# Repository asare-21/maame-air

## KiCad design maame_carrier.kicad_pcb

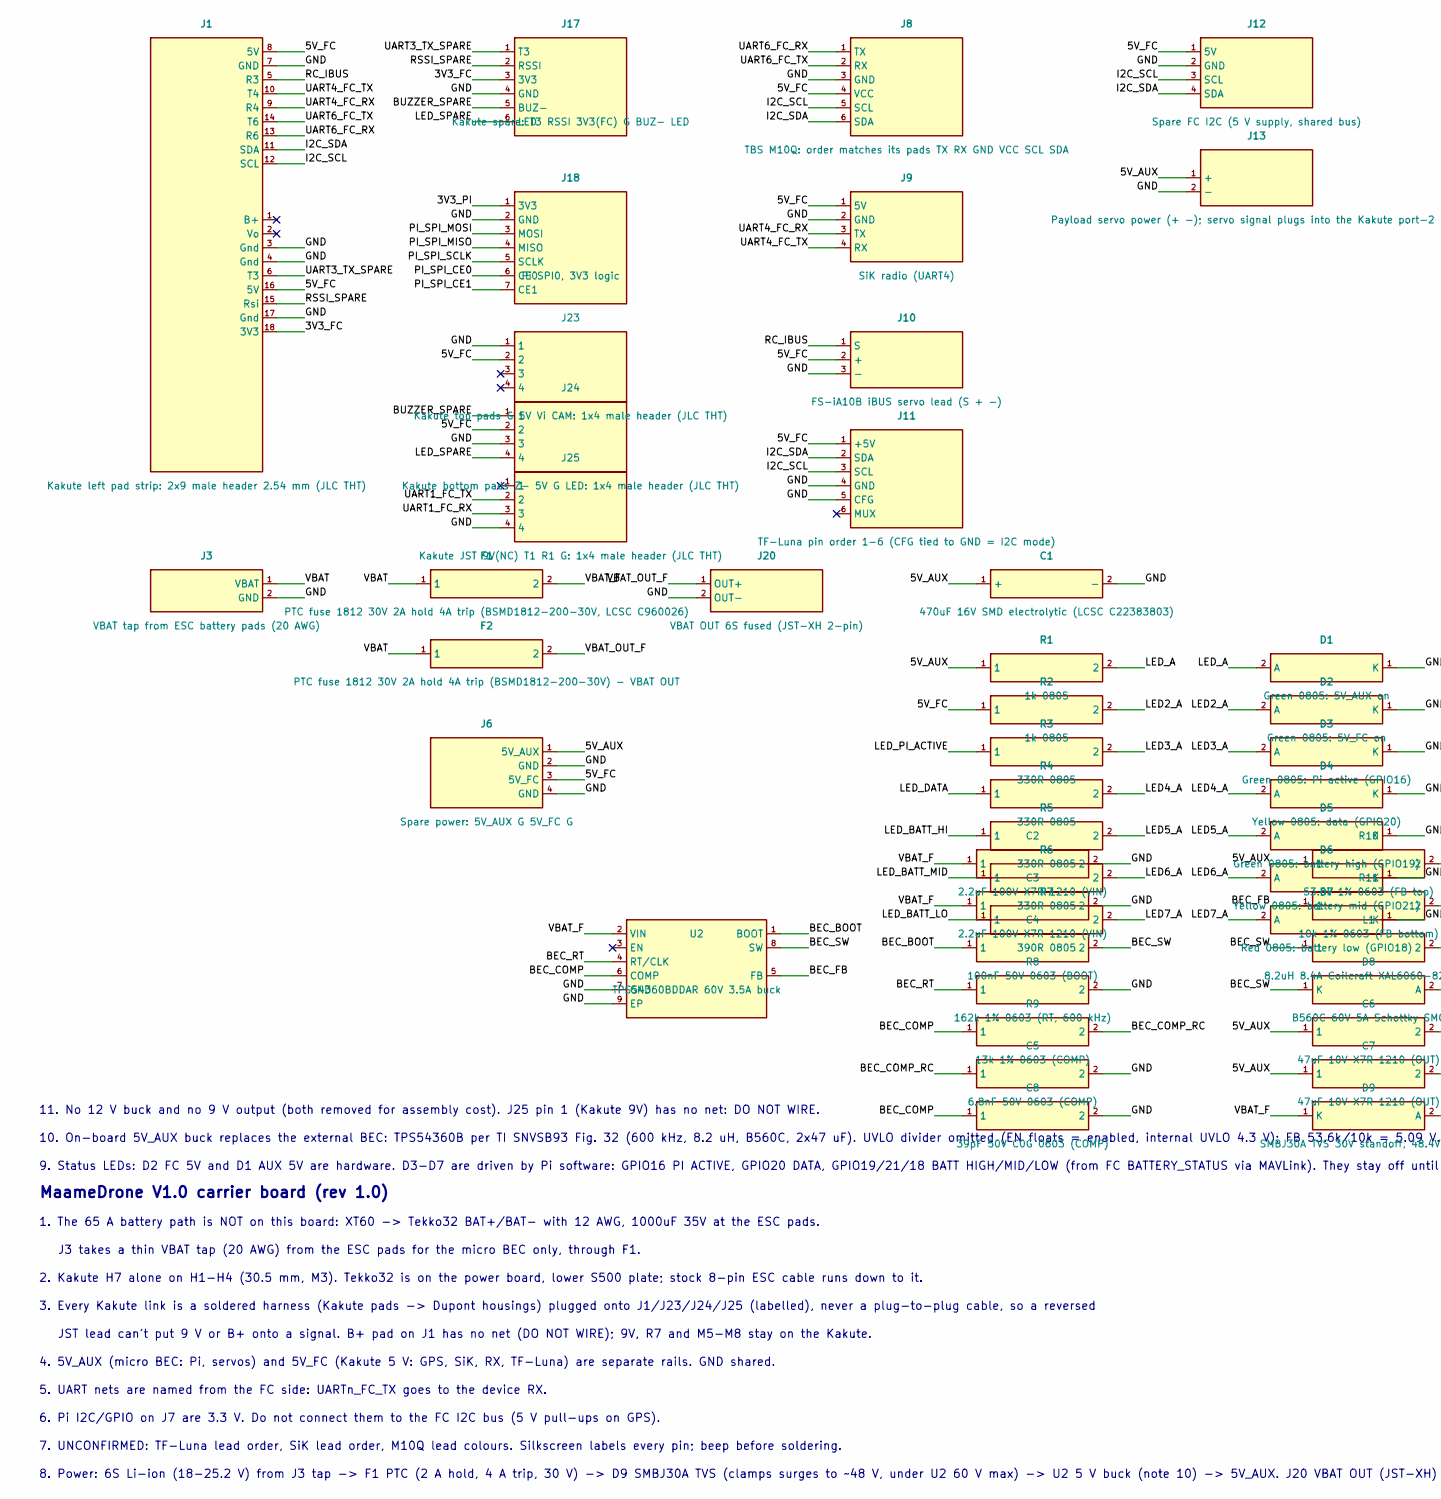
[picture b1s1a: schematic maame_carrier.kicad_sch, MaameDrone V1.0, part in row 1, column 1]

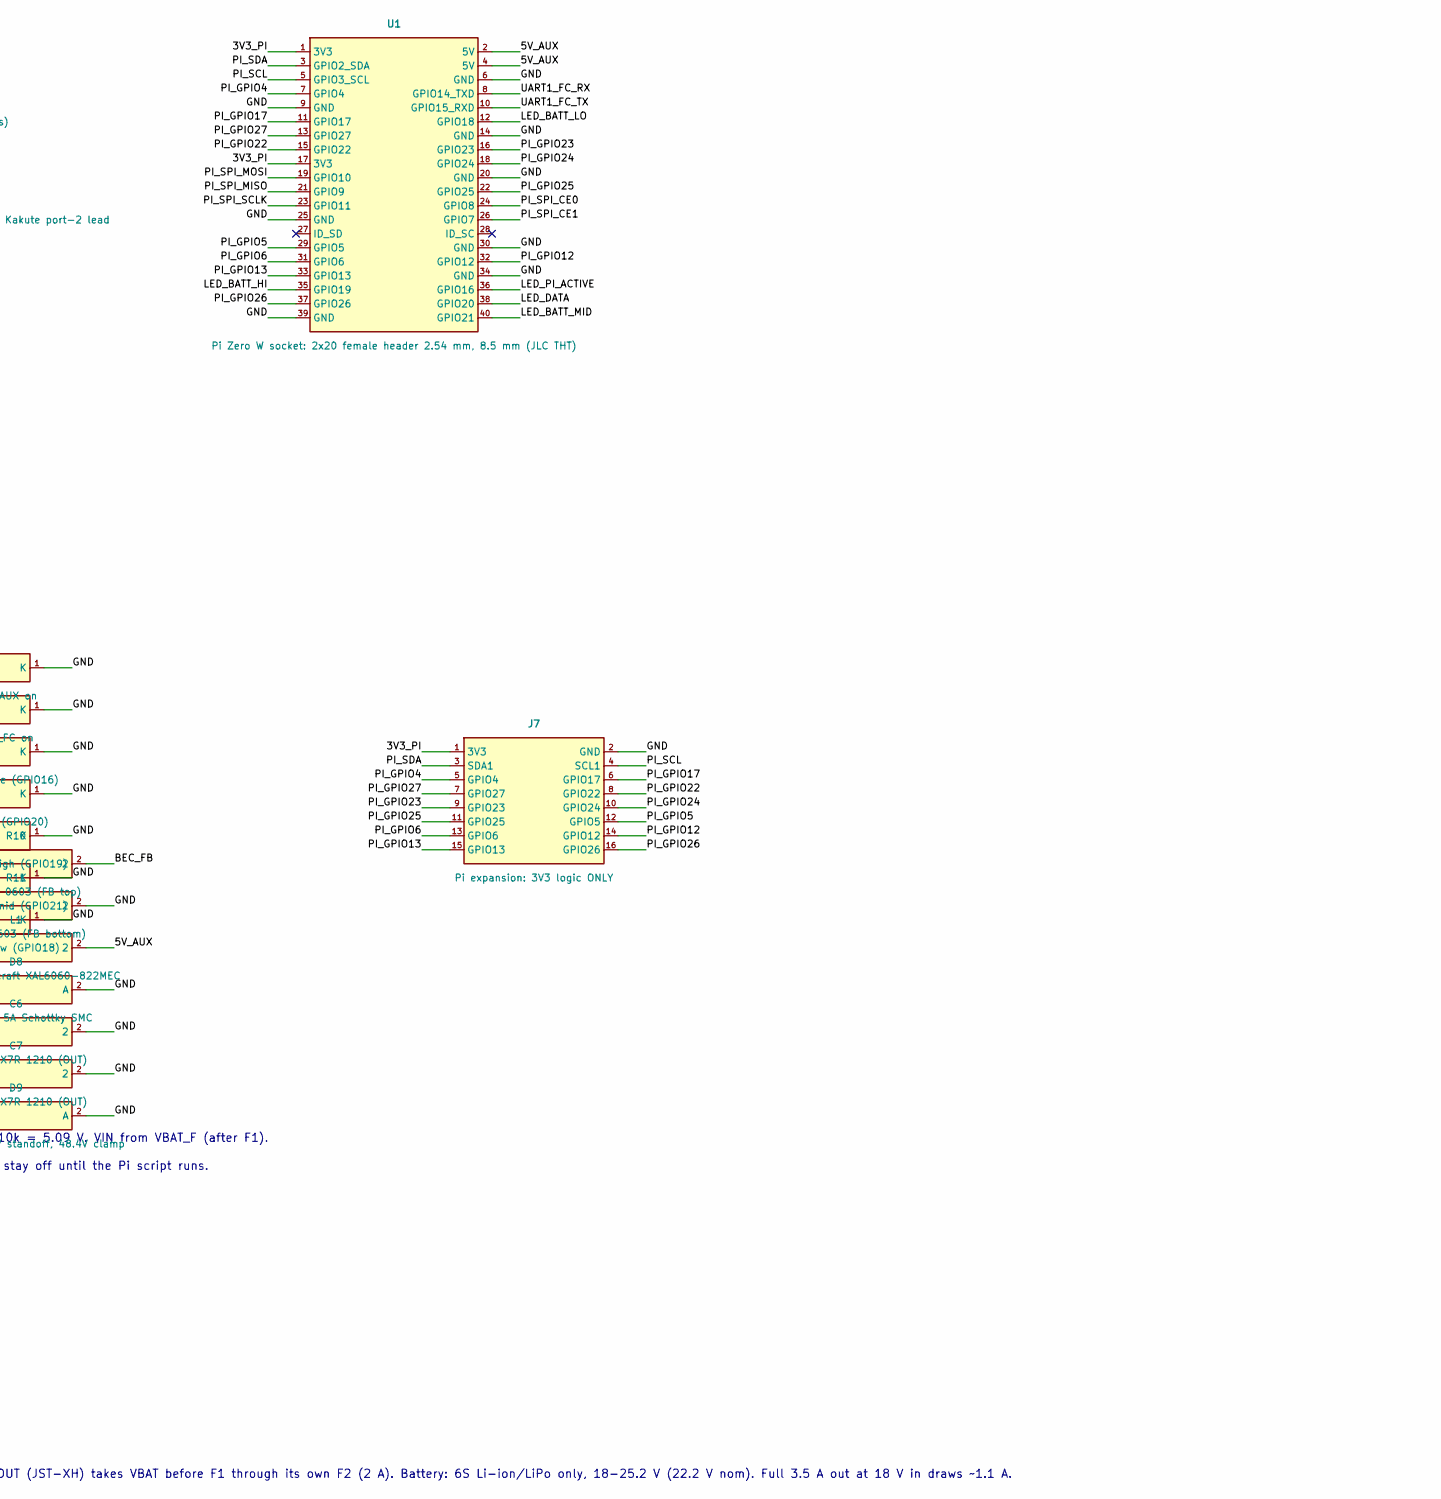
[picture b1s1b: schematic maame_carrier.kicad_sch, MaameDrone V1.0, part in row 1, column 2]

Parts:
C1: 470uF 16V SMD electrolytic (LCSC C22383803); CP_Elec_6.3x7.7; LCSC C22383803
C2, C3: 2.2uF 100V X7R 1210 (VIN); C_1210_3225Metric; LCSC C153036
C4: 100nF 50V 0603 (BOOT); C_0603_1608Metric; LCSC C14663
C5: 6.8nF 50V 0603 (COMP); C_0603_1608Metric; LCSC C1631
C6, C7: 47uF 10V X7R 1210 (OUT); C_1210_3225Metric; LCSC C84494
C8: 39pF 50V C0G 0603 (COMP); C_0603_1608Metric; LCSC C107049
D1: Green 0805: 5V_AUX on; LED_0805_2012Metric_Pad1.15x1.40mm_HandSolder; LCSC C2297
D2: Green 0805: 5V_FC on; LED_0805_2012Metric_Pad1.15x1.40mm_HandSolder; LCSC C2297
D3: Green 0805: Pi active (GPIO16); LED_0805_2012Metric_Pad1.15x1.40mm_HandSolder; LCSC C2297
D4: Yellow 0805: data (GPIO20); LED_0805_2012Metric_Pad1.15x1.40mm_HandSolder; LCSC C2296
D5: Green 0805: battery high (GPIO19); LED_0805_2012Metric_Pad1.15x1.40mm_HandSolder; LCSC C2297
D6: Yellow 0805: battery mid (GPIO21); LED_0805_2012Metric_Pad1.15x1.40mm_HandSolder; LCSC C2296
D7: Red 0805: battery low (GPIO18); LED_0805_2012Metric_Pad1.15x1.40mm_HandSolder; LCSC C84256
D8: B560C 60V 5A Schottky SMC; D_SMC; LCSC C85100
D9: SMBJ30A TVS 30V standoff, 48.4V clamp; D_SMB; LCSC C113998
F1, F2: PTC fuse 1812 30V 2A hold 4A trip (BSMD1812-200-3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; Fuse_1812_4532Metric_Pad1.30x3.40mm_HandSolder; LCSC C960026
J1: Kakute left pad strip: 2x9 male header 2.54 mm (J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; PinHeader_2x09_P2.54mm_Vertical; LCSC C42372517
J3: VBAT tap from ESC battery pads (20 AWG); SolderWire-0.5sqmm_1x02_P4.6mm_D0.9mm_OD2.1mm
J6: Spare power: 5V_AUX G 5V_FC G; PinHeader_1x04_P2.54mm_Vertical
J7: Pi expansion: 3V3 logic ONLY; PinHeader_2x08_P2.54mm_Vertical
J8: TBS M10Q: order matches its pads TX RX GND VCC SC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; PinHeader_1x06_P2.54mm_Vertical
J9: SiK radio (UART4); PinHeader_1x04_P2.54mm_Vertical
J10: FS-iA10B iBUS servo lead (S + -); PinHeader_1x03_P2.54mm_Vertical
J11: TF-Luna pin order 1-6 (CFG tied to GND = I2C mode); PinHeader_1x06_P2.54mm_Vertical
J12: Spare FC I2C (5 V supply, shared bus); PinHeader_1x04_P2.54mm_Vertical
J13: Payload servo power (+ -); servo signal plugs int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; PinHeader_1x02_P2.54mm_Vertical
J17: Kakute spare: T3 RSSI 3V3(FC) G BUZ- LED; PinHeader_1x06_P2.54mm_Vertical
J18: Pi SPI0, 3V3 logic; PinHeader_1x07_P2.54mm_Vertical
J20: VBAT OUT 6S fused (JST-XH 2-pin); JST_XH_B2B-XH-A_1x02_P2.50mm_Vertical
J23: Kakute top pads G 5V Vi CAM: 1x4 male header (JLC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; PinHeader_1x04_P2.54mm_Vertical; LCSC C32713270
J24: Kakute bottom pads Z- 5V G LED: 1x4 male header (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; PinHeader_1x04_P2.54mm_Vertical; LCSC C32713270
J25: Kakute JST 9V(NC) T1 R1 G: 1x4 male header (JLC T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; PinHeader_1x04_P2.54mm_Vertical; LCSC C32713270
L1: 8.2uH 8.4A Coilcraft XAL6060-822MEC; L_Coilcraft_XAL6060-XXX; LCSC C19191627
R1, R2: 1k 0805; R_0805_2012Metric_Pad1.20x1.40mm_HandSolder; LCSC C17513
R3, R4, R5, R6: 330R 0805; R_0805_2012Metric_Pad1.20x1.40mm_HandSolder; LCSC C17630
R7: 390R 0805; R_0805_2012Metric_Pad1.20x1.40mm_HandSolder; LCSC C17655
R8: 162k 1% 0603 (RT, 600 kHz); R_0603_1608Metric; LCSC C227607
R9: 13k 1% 0603 (COMP); R_0603_1608Metric; LCSC C22797
R10: 53.6k 1% 0603 (FB top); R_0603_1608Metric; LCSC C23074
R11: 10k 1% 0603 (FB bottom); R_0603_1608Metric; LCSC C25804
U1: Pi Zero W socket: 2x20 female header 2.54 mm, 8.5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; Pi_Zero_Socketed_FaceDown_MountingHoles; LCSC C5124634
U2: TPS54360BDDAR 60V 3.5A buck; TI_SO-PowerPAD-8_ThermalVias; LCSC C524806

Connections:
/3V3_FC: J1.18 (3V3), J17.3 (3V3)
/3V3_PI: J7.1 (3V3), J18.1 (3V3), U1.1 (3V3), U1.17 (3V3)
/5V_AUX: C1.1 (+), C6.1, C7.1, J6.1 (5V_AUX), J13.1 (+), L1.2, R1.1, R10.1, U1.2 (5V), U1.4 (5V)
/5V_FC: J1.8 (5V), J1.16 (5V), J6.3 (5V_FC), J8.4 (VCC), J9.1 (5V), J10.2 (+), J11.1 (+5V), J12.1 (5V), J23.2, J24.2, R2.1
/BEC_BOOT: C4.1, U2.1 (BOOT)
/BEC_COMP: C8.1, R9.1, U2.6 (COMP)
/BEC_COMP_RC: C5.1, R9.2
/BEC_FB: R10.2, R11.1, U2.5 (FB)
/BEC_RT: R8.1, U2.4 (RT/CLK)
/BEC_SW: C4.2, D8.1 (K), L1.1, U2.8 (SW)
/BUZZER_SPARE: J17.5 (BUZ-), J24.1
/GND: C1.2 (-), C2.2, C3.2, C5.2, C6.2, C7.2, C8.2, D1.1 (K), D2.1 (K), D3.1 (K), D4.1 (K), D5.1 (K), D6.1 (K), D7.1 (K), D8.2 (A), D9.2 (A), J1.3 (Gnd), J1.4 (Gnd), J1.7 (GND), J1.17 (Gnd), J3.2 (GND), J6.2 (GND), J6.4 (GND), J7.2 (GND), J8.3 (GND), J9.2 (GND), J10.3 (-), J11.4 (GND), J11.5 (CFG), J12.2 (GND), J13.2 (-), J17.4 (GND), J18.2 (GND), J20.2 (OUT-), J23.1, J24.3, J25.4, R8.2, R11.2, U1.6 (GND), U1.9 (GND), U1.14 (GND), U1.20 (GND), U1.25 (GND), U1.30 (GND), U1.34 (GND), U1.39 (GND), U2.7 (GND), U2.9 (EP)
/I2C_SCL: J1.12 (SCL), J8.5 (SCL), J11.3 (SCL), J12.3 (SCL)
/I2C_SDA: J1.11 (SDA), J8.6 (SDA), J11.2 (SDA), J12.4 (SDA)
/LED2_A: D2.2 (A), R2.2
/LED3_A: D3.2 (A), R3.2
/LED4_A: D4.2 (A), R4.2
/LED5_A: D5.2 (A), R5.2
/LED6_A: D6.2 (A), R6.2
/LED7_A: D7.2 (A), R7.2
/LED_A: D1.2 (A), R1.2
/LED_BATT_HI: R5.1, U1.35 (GPIO19)
/LED_BATT_LO: R7.1, U1.12 (GPIO18)
/LED_BATT_MID: R6.1, U1.40 (GPIO21)
/LED_DATA: R4.1, U1.38 (GPIO20)
/LED_PI_ACTIVE: R3.1, U1.36 (GPIO16)
/LED_SPARE: J17.6 (LED), J24.4
/PI_GPIO4: J7.5 (GPIO4), U1.7 (GPIO4)
/PI_GPIO5: J7.12 (GPIO5), U1.29 (GPIO5)
/PI_GPIO6: J7.13 (GPIO6), U1.31 (GPIO6)
/PI_GPIO12: J7.14 (GPIO12), U1.32 (GPIO12)
/PI_GPIO13: J7.15 (GPIO13), U1.33 (GPIO13)
/PI_GPIO17: J7.6 (GPIO17), U1.11 (GPIO17)
/PI_GPIO22: J7.8 (GPIO22), U1.15 (GPIO22)
/PI_GPIO23: J7.9 (GPIO23), U1.16 (GPIO23)
/PI_GPIO24: J7.10 (GPIO24), U1.18 (GPIO24)
/PI_GPIO25: J7.11 (GPIO25), U1.22 (GPIO25)
/PI_GPIO26: J7.16 (GPIO26), U1.37 (GPIO26)
/PI_GPIO27: J7.7 (GPIO27), U1.13 (GPIO27)
/PI_SCL: J7.4 (SCL1), U1.5 (GPIO3_SCL)
/PI_SDA: J7.3 (SDA1), U1.3 (GPIO2_SDA)
/PI_SPI_CE0: J18.6 (CE0), U1.24 (GPIO8)
/PI_SPI_CE1: J18.7 (CE1), U1.26 (GPIO7)
/PI_SPI_MISO: J18.4 (MISO), U1.21 (GPIO9)
/PI_SPI_MOSI: J18.3 (MOSI), U1.19 (GPIO10)
/PI_SPI_SCLK: J18.5 (SCLK), U1.23 (GPIO11)
/RC_IBUS: J1.5 (R3), J10.1 (S)
/RSSI_SPARE: J1.15 (Rsi), J17.2 (RSSI)
/UART1_FC_RX: J25.3, U1.8 (GPIO14_TXD)
/UART1_FC_TX: J25.2, U1.10 (GPIO15_RXD)
/UART3_TX_SPARE: J1.6 (T3), J17.1 (T3)
/UART4_FC_RX: J1.9 (R4), J9.3 (TX)
/UART4_FC_TX: J1.10 (T4), J9.4 (RX)
/UART6_FC_RX: J1.13 (R6), J8.1 (TX)
/UART6_FC_TX: J1.14 (T6), J8.2 (RX)
/VBAT: F1.1, F2.1, J3.1 (VBAT)
/VBAT_F: C2.1, C3.1, D9.1 (K), F1.2, U2.2 (VIN)
/VBAT_OUT_F: F2.2, J20.1 (OUT+)

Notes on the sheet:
J3 takes a thin VBAT tap (20 AWG) from the ESC pads for the micro BEC only, through F1.
MaameDrone V1.0 carrier board (rev 1.0)
5. UART nets are named from the FC side: UARTn_FC_TX goes to the device RX.
6. Pi I2C/GPIO on J7 are 3.3 V. Do not connect them to the FC I2C bus (5 V pull-ups on GPS).
3. Every Kakute link is a soldered harness (Kakute pads -> Dupont housings) plugged onto J1/J23/J24/J25 (labelled), never a plug-to-plug cable, so a reversed
1. The 65 A battery path is NOT on this board: XT60 -> Tekko32 BAT+/BAT- with 12 AWG, 1000uF 35V at the ESC pads.
4. 5V_AUX (micro BEC: Pi, servos) and 5V_FC (Kakute 5 V: GPS, SiK, RX, TF-Luna) are separate rails. GND shared.
8. Power: 6S Li-ion (18-25.2 V) from J3 tap -> F1 PTC (2 A hold, 4 A trip, 30 V) -> D9 SMBJ30A TVS (clamps surges to ~48 V, under U2 60 V max) -> U2 5 V buck (note 10) -> 5V_AUX. J20 VBAT OUT (JST-XH) takes VBAT before F1 through its own F2 (2 A). Battery: 6S Li-ion/LiPo only, 18-25.2 V (22.2 V nom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
7. UNCONFIRMED: TF-Luna lead order, SiK lead order, M10Q lead colours. Silkscreen labels every pin; beep before soldering.
2. Kakute H7 alone on H1-H4 (30.5 mm, M3). Tekko32 is on the power board, lower S500 plate; stock 8-pin ESC cable runs down to it.
JST lead can't put 9 V or B+ onto a signal. B+ pad on J1 has no net (DO NOT WIRE); 9V, R7 and M5-M8 stay on the Kakute.
9. Status LEDs: D2 FC 5V and D1 AUX 5V are hardware. D3-D7 are driven by Pi software: GPIO16 PI ACTIVE, GPIO20 DATA, GPIO19/21/18 BATT HIGH/MID/LOW (from FC BATTERY_STATUS via MAVLink). They stay off until the Pi script runs.
10. On-board 5V_AUX buck replaces the external BEC: TPS54360B per TI SNVSB93 Fig. 32 (600 kHz, 8.2 uH, B560C, 2x47 uF). UVLO divider omitted (EN floats = enabled, internal UVLO 4.3 V); FB 53.6k/10k = 5.09 V. VIN from VBAT_F (after F1).
11. No 12 V buck and no 9 V output (both removed for assembly cost). J25 pin 1 (Kakute 9V) has no net: DO NOT WIRE.

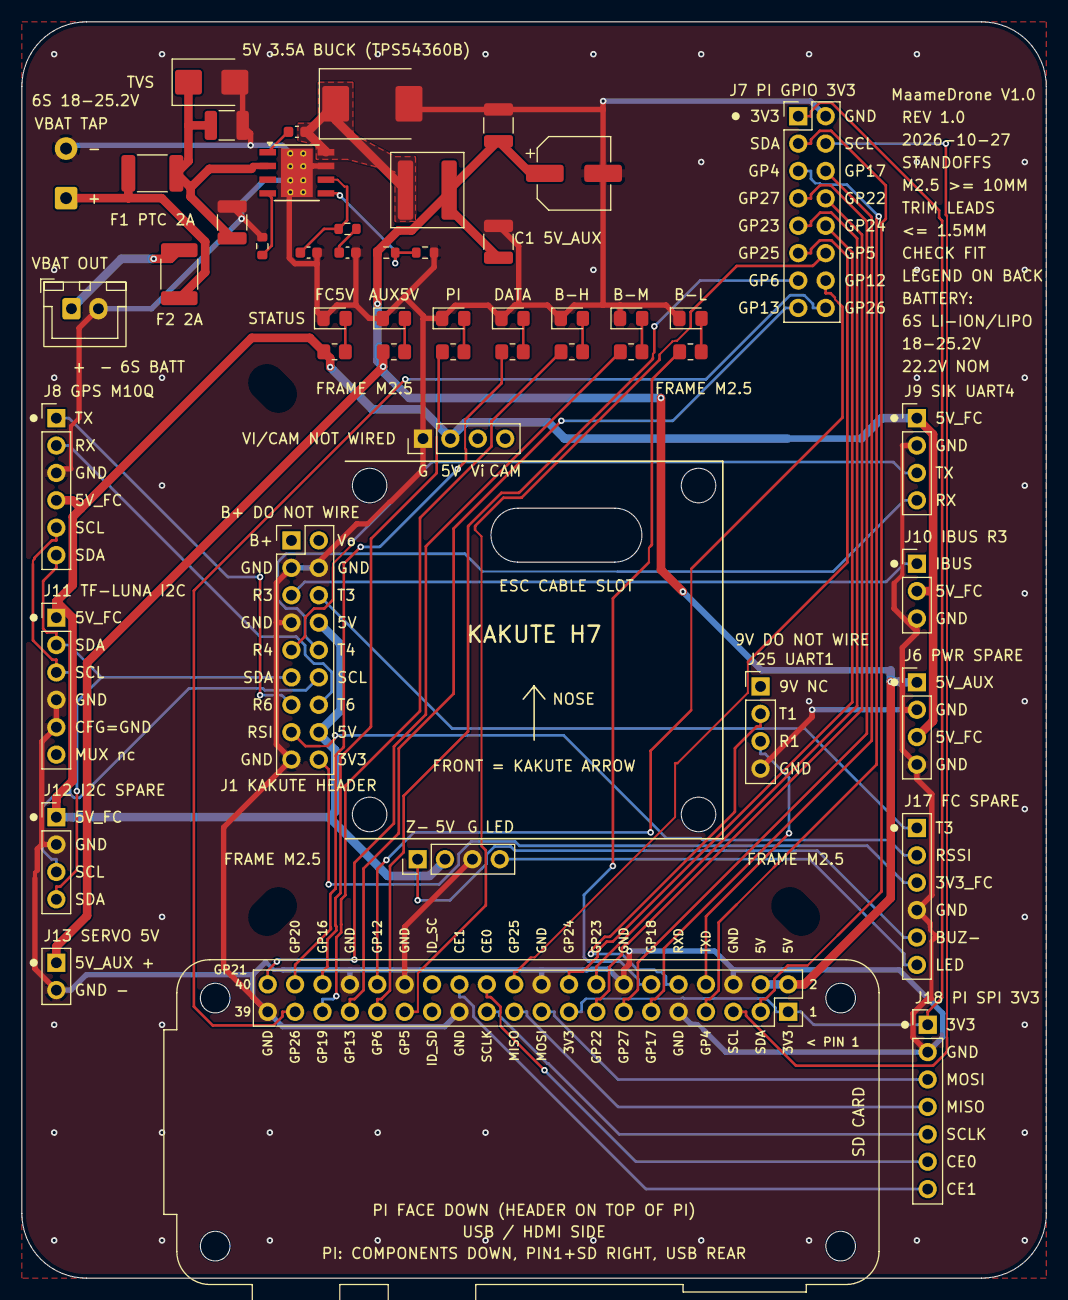
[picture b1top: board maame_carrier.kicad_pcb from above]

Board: 2 copper layers, 95.0 x 116.5 mm, 57 parts (0 on the bottom side), 58 nets.

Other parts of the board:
H1, H2, H3, H4: M3 FC hole; MountingHole_3.2mm_M3
H5, H6, H7, H8: M2.5 frame mount, 48.5 mm square, radial slot; MountingHole_2.7mm_M2.5

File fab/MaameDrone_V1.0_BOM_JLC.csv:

Comment,Designator,Footprint,LCSC Part #
470uF 16V SMD electrolytic (LCSC C22383803),C1,CP_Elec_6.3x7.7,C22383803
2.2uF 100V X7R 1210 (VIN),"C2,C3",C_1210_3225Metric,C153036
100nF 50V 0603 (BOOT),C4,C_0603_1608Metric,C14663
6.8nF 50V 0603 (COMP),C5,C_0603_1608Metric,C1631
47uF 10V X7R 1210 (OUT),"C6,C7",C_1210_3225Metric,C84494
39pF 50V C0G 0603 (COMP),C8,C_0603_1608Metric,C107049
Green 0805: 5V_AUX on,"D1,D2,D3,D5",LED_0805_2012Metric_Pad1.15x1.40mm_HandSolder,C2297
Yellow 0805: data (GPIO20),"D4,D6",LED_0805_2012Metric_Pad1.15x1.40mm_HandSolder,C2296
Red 0805: battery low (GPIO18),D7,LED_0805_2012Metric_Pad1.15x1.40mm_HandSolder,C84256
B560C 60V 5A Schottky SMC,D8,D_SMC,C85100
"SMBJ30A TVS 30V standoff, 48.4V clamp",D9,D_SMB,C113998
"PTC fuse 1812 30V 2A hold 4A trip (BSMD1812-200-30V, LCSC C960026)","F1,F2",Fuse_1812_4532Metric_Pad1.30x3.40mm_HandSolder,C960026
8.2uH 8.4A Coilcraft XAL6060-822MEC,L1,L_Coilcraft_XAL6060-XXX,C19191627
1k 0805,"R1,R2",R_0805_2012Metric_Pad1.20x1.40mm_HandSolder,C17513
330R 0805,"R3,R4,R5,R6",R_0805_2012Metric_Pad1.20x1.40mm_HandSolder,C17630
390R 0805,R7,R_0805_2012Metric_Pad1.20x1.40mm_HandSolder,C17655
"162k 1% 0603 (RT, 600 kHz)",R8,R_0603_1608Metric,C227607
13k 1% 0603 (COMP),R9,R_0603_1608Metric,C22797
53.6k 1% 0603 (FB top),R10,R_0603_1608Metric,C23074
10k 1% 0603 (FB bottom),R11,R_0603_1608Metric,C25804
TPS54360BDDAR 60V 3.5A buck,U2,TI_SO-PowerPAD-8_ThermalVias,C524806

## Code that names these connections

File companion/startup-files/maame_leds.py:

#!/usr/bin/env python3
"""Drives the five Pi-controlled status LEDs on the Maame carrier board.

All LEDs are active high (GPIO -> resistor -> LED -> GND):
    GPIO16  PI     green   on while the companion script runs (blinks if the FC goes quiet)
    GPIO20  DATA   yellow  flashes on each MAVLink message to or from the FC
    GPIO19  B-H    green   battery high
    GPIO21  B-M    yellow  battery mid
    GPIO18  B-L    red     battery low (flashes when the FC reports a low-battery failsafe)

Battery level comes from the FC over MAVLink: SYS_STATUS.battery_remaining (%)
when the FC reports it, otherwise SYS_STATUS.voltage_battery per cell. The pack
is a 6S Li-ion. BATTERY_STATUS.charge_state LOW or worse makes B-L flash.

CompanionLink (maame_ready.py) calls on_message() for every message it reads and
on_sent() for every message it sends, plus update() once per loop.
"""
import time

CELLS = 6
PCT_HIGH = 50          # >= this: B-H
PCT_MID = 25           # >= this: B-M, below: B-L
CELL_V_HIGH = 3.70     # voltage fallback, per cell
CELL_V_MID = 3.50
DATA_FLASH_S = 0.08   # long enough to see at a 20 Hz main loop
FC_QUIET_S = 3.0
BLINK_PERIOD_S = 0.5
CHARGE_STATE_LOW = 2   # MAV_BATTERY_CHARGE_STATE_LOW
VOLT_SMOOTHING = 0.1   # per SYS_STATUS (1 Hz default): ~10 s time constant

PIN_PI, PIN_DATA, PIN_BH, PIN_BM, PIN_BL = 16, 20, 19, 21, 18


def battery_level(remaining_pct, voltage_mv):
    """Return 'high', 'mid', 'low' or None (no data)."""
    if remaining_pct is not None and 0 <= remaining_pct <= 100:
        if remaining_pct >= PCT_HIGH:
            return "high"
        return "mid" if remaining_pct >= PCT_MID else "low"
    if voltage_mv:
        cell = voltage_mv / 1000.0 / CELLS
        if cell > CELL_V_HIGH:
            return "high"
        return "mid" if cell >= CELL_V_MID else "low"
    return None


class StatusLeds:
    def __init__(self, led_factory=None):
        if led_factory is None:
            from gpiozero import LED
            led_factory = LED
        self.pi, self.data, self.bh, self.bm, self.bl = (
            led_factory(p) for p in (PIN_PI, PIN_DATA, PIN_BH, PIN_BM, PIN_BL))
        self.level = None
        self.failsafe = False
        self._data_until = 0.0
        self._last_fc_msg = 0.0
        self._volt_mv = None

    def on_message(self, msg, now=None):
        now = time.monotonic() if now is None else now
        self._flash_data(now)
        if msg.get_srcComponent() == 1:  # MAV_COMP_ID_AUTOPILOT1
            self._last_fc_msg = now
        kind = msg.get_type()
        if kind == "SYS_STATUS":
            remaining = msg.battery_remaining if msg.battery_remaining >= 0 else None
            voltage = msg.voltage_battery if 0 < msg.voltage_battery < 65535 else None
            if voltage is not None:
                # smooth throttle sag so the LEDs don't flicker between levels
                self._volt_mv = voltage if self._volt_mv is None else (
                    self._volt_mv + VOLT_SMOOTHING * (voltage - self._volt_mv))
            self.level = battery_level(remaining, self._volt_mv)
        elif kind == "BATTERY_STATUS" and msg.id == 0:
            self.failsafe = getattr(msg, "charge_state", 0) >= CHARGE_STATE_LOW

    def on_sent(self, now=None):
        self._flash_data(time.monotonic() if now is None else now)

    def update(self, now=None):
        now = time.monotonic() if now is None else now
        blink_on = int(now / BLINK_PERIOD_S) % 2 == 0
        fc_ok = now - self._last_fc_msg < FC_QUIET_S
        self._set(self.pi, True if fc_ok else blink_on)
        self._set(self.data, now < self._data_until)
        self._set(self.bh, self.level == "high")
        self._set(self.bm, self.level == "mid")
        low = self.level == "low" or self.failsafe
        self._set(self.bl, low and (blink_on if self.failsafe else True))

    def off(self):
        for led in (self.pi, self.data, self.bh, self.bm, self.bl):
            led.off()

    def _flash_data(self, now):
        self._data_until = now + DATA_FLASH_S

    @staticmethod
    def _set(led, on):
        led.on() if on else led.off()
